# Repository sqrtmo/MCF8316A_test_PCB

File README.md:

# MCF8316A test board (KiCAD version)

This is meant to be an easy and cheaper way to test the MCF8316A chip. If you do not have access, 
or you don't want to buy the evaluation board from TI(see datasheet in doc subfolder), 
you can use this PCB in combiation [with my micropython driver made for raspberry pi pico](https://github.com/sqrtmo/MCF8316A_driver?tab=readme-ov-file) to setup and 
test the chip with your desired BLDC motor.

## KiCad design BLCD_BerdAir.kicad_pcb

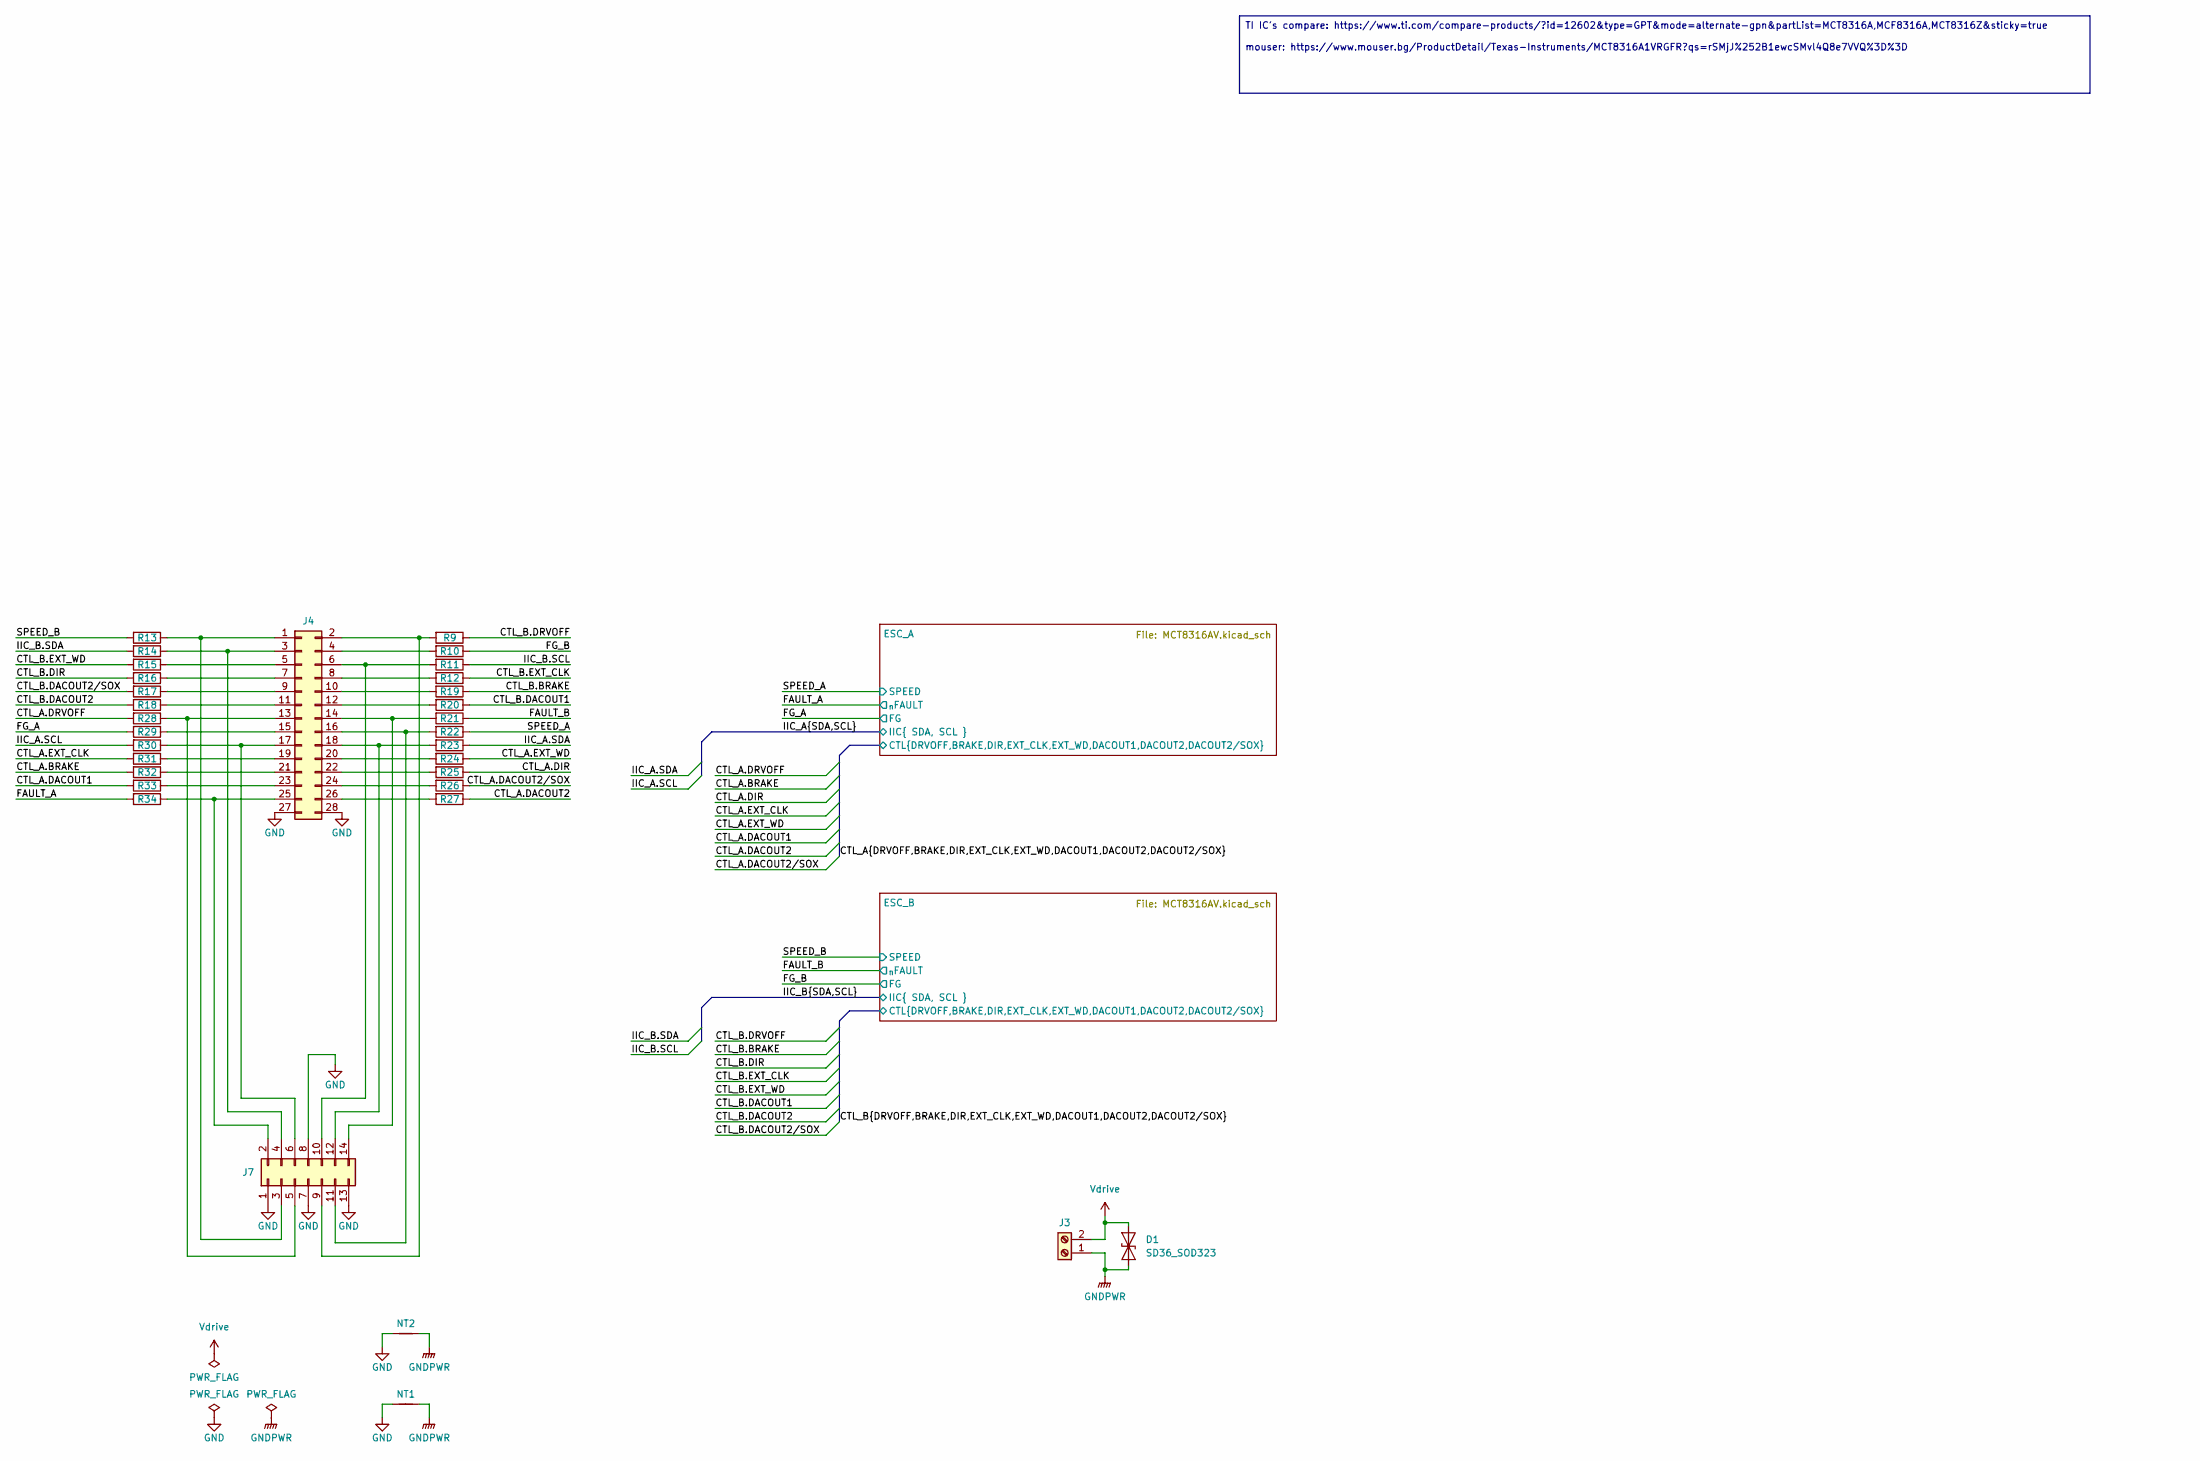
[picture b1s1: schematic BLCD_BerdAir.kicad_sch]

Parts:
D1: SD36_SOD323; D_SOD-323
J3: Screw_Terminal_01x03; TerminalBlock_Phoenix_MKDS-1,5-2-5.08_1x02_P5.08mm_Horizont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
J4: Conn_02x12_Odd_Even; PinHeader_2x14_P2.54mm_Vertical
J7: Conn_02x06_Top_Bottom; PinHeader_2x07_P2.54mm_Vertical
NT1, NT2: NetTie_2; NetTie-2_SMD_Pad0.5mm
R9, R10, R11, R12, R13, R14, R15, R16, R17, R18, R19, R20, R21, R22, R23, R24, R25, R26, R27, R28, R29, R30, R31, R32, R33, R34: 100R; R_0402_1005Metric

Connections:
/CTL_A.BRAKE: R32.2; also elsewhere on the board
/CTL_A.DACOUT1: R33.2; also elsewhere on the board
/CTL_A.DACOUT2: R27.1; also elsewhere on the board
/CTL_A.DACOUT2/SOX: R26.1; also elsewhere on the board
/CTL_A.DIR: R25.1; also elsewhere on the board
/CTL_A.DRVOFF: R28.2; also elsewhere on the board
/CTL_A.EXT_CLK: R31.2; also elsewhere on the board
/CTL_A.EXT_WD: R24.1; also elsewhere on the board
/CTL_B.BRAKE: R19.1; also elsewhere on the board
/CTL_B.DACOUT1: R20.1; also elsewhere on the board
/CTL_B.DACOUT2: R18.2; also elsewhere on the board
/CTL_B.DACOUT2/SOX: R17.2; also elsewhere on the board
/CTL_B.DIR: R16.2; also elsewhere on the board
/CTL_B.DRVOFF: R9.1; also elsewhere on the board
/CTL_B.EXT_CLK: R12.1; also elsewhere on the board
/CTL_B.EXT_WD: R15.2; also elsewhere on the board
/FAULT_A: R34.2; also elsewhere on the board
/FAULT_B: R21.1; also elsewhere on the board
/FG_A: R29.2; also elsewhere on the board
/FG_B: R10.1; also elsewhere on the board
/IIC_A.SCL: R30.2; also elsewhere on the board
/IIC_A.SDA: R23.1; also elsewhere on the board
/IIC_B.SCL: R11.1; also elsewhere on the board
/IIC_B.SDA: R14.2; also elsewhere on the board
/SPEED_A: R22.1; also elsewhere on the board
/SPEED_B: R13.2; also elsewhere on the board
GND: J4.27, J4.28, J7.1, J7.7, J7.8, J7.13, NT1.1, NT2.1; also elsewhere on the board
GNDPWR: D1.1 (A1), J3.1, NT1.2, NT2.2; also elsewhere on the board
unnamed: J4.1, J7.3, R13.1
unnamed: J4.2, J7.9, R9.2
unnamed: J4.3, J7.4, R14.1
unnamed: J4.4, R10.2
unnamed: J4.5, R15.1
unnamed: J4.6, J7.10, R11.2
unnamed: J4.7, R16.1
unnamed: J4.8, R12.2
unnamed: J4.9, R17.1
unnamed: J4.10, R19.2
unnamed: J4.11, R18.1
unnamed: J4.12, R20.2
unnamed: J4.13, J7.5, R28.1
unnamed: J4.14, J7.14, R21.2
unnamed: J4.15, R29.1
unnamed: J4.16, J7.11, R22.2
unnamed: J4.17, J7.6, R30.1
unnamed: J4.18, J7.12, R23.2
unnamed: J4.19, R31.1
unnamed: J4.20, R24.2
unnamed: J4.21, R32.1
unnamed: J4.22, R25.2
unnamed: J4.23, R33.1
unnamed: J4.24, R26.2
unnamed: J4.25, J7.2, R34.1
unnamed: J4.26, R27.2
Vdrive: D1.2 (A2), J3.2; also elsewhere on the board

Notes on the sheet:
TI IC's compare: https://www.ti.com/compare-products/?id=12602&type=GPT&mode=alternate-gpn&partList=MCT8316A,MCF8316A,MCT8316Z&sticky=true mouser: https://www.mouser.bg/ProductDetail/Texas-Instruments/MCT8316A1VRGFR?qs=rSMjJ%252B1ewcSMvl4Q8e7VVQ%3D%3D

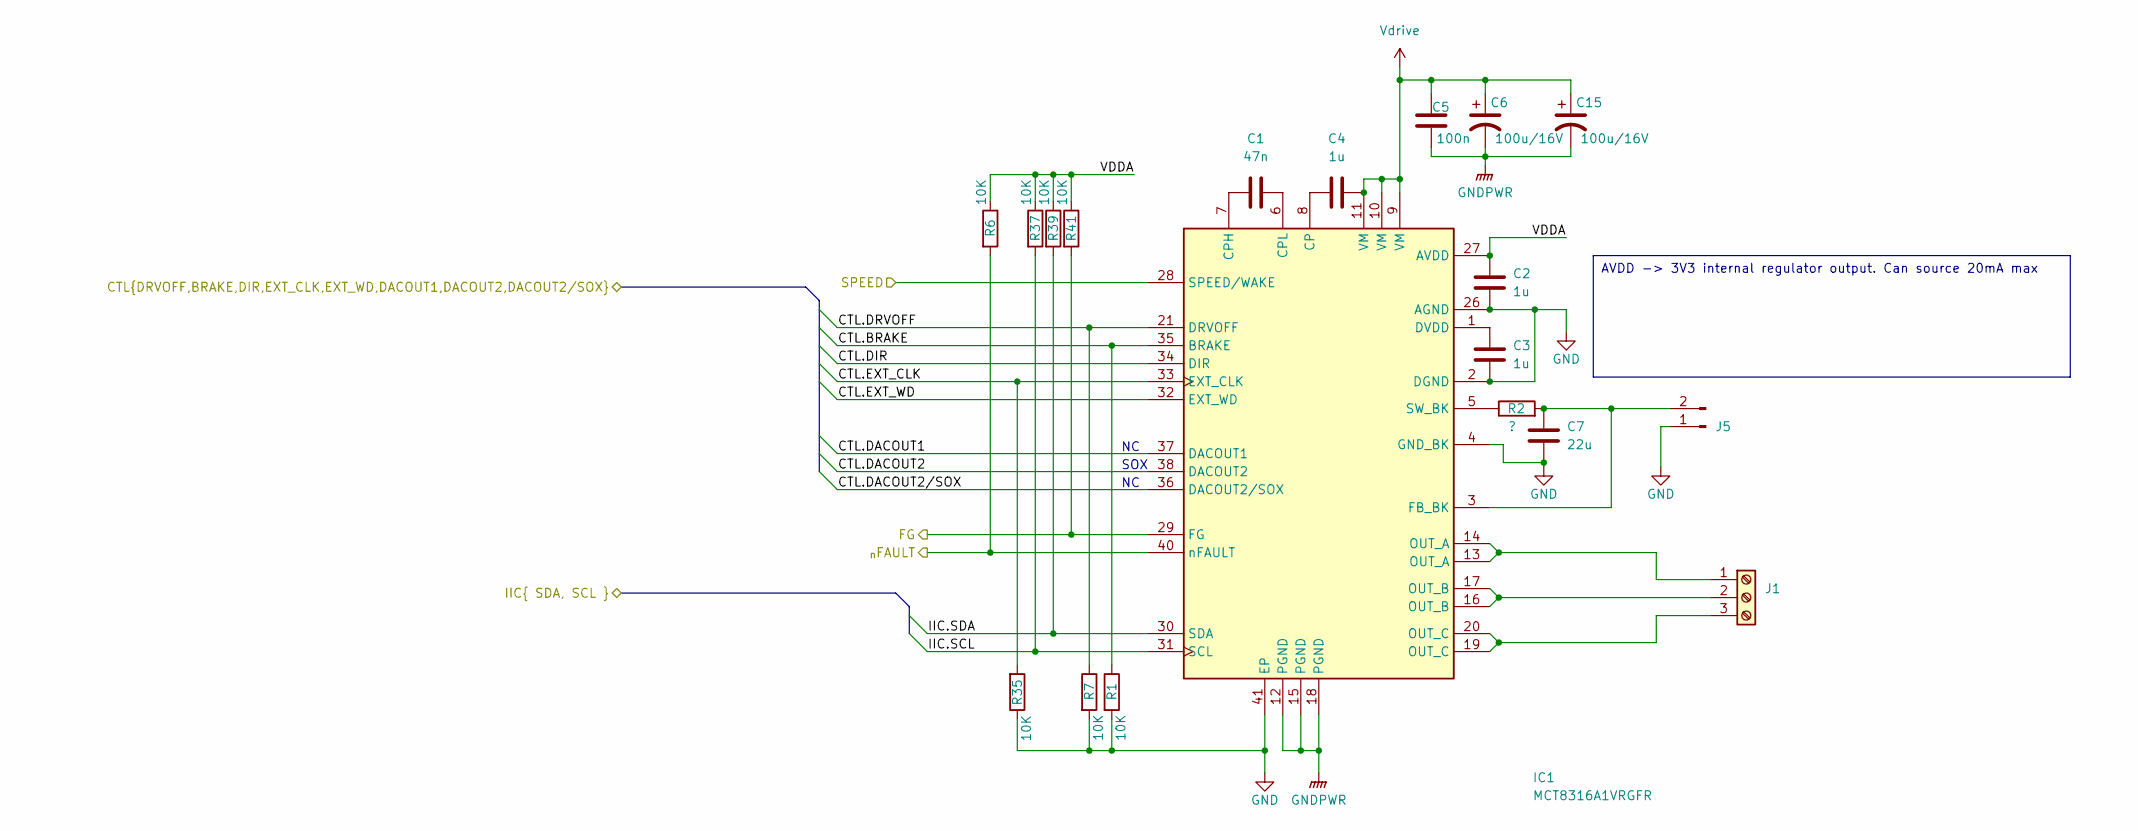
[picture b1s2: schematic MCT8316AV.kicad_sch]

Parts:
C1: 47n; C_0402_1005Metric
C2, C3, C4: 1u; C_0402_1005Metric
C5: 100n; C_0603_1608Metric
C6, C15: 100u/16V; CP_EIA-7132-28_AVX-C
C7: 22u; C_0603_1608Metric
IC1: MCT8316A1VRGFR; QFN50P500X700X100-41N-D; Manufacturer_Part_Number MCT8316A1VRGFR; Mouser Part Number 595-MCT8316A1VRGFR
J1: Screw_Terminal_01x03; TerminalBlock_Phoenix_MKDS-1,5-3-5.08_1x03_P5.08mm_Horizont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
J5: Conn_01x02_Pin; PinHeader_1x02_P1.27mm_Vertical
R1, R6, R7, R35, R37, R39, R41: 10K; R_0402_1005Metric
R2: ?; R_1210_3225Metric

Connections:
/CTL_A.BRAKE: IC1.35 (BRAKE), R1.1; also elsewhere on the board
/CTL_A.DACOUT1: IC1.37 (DACOUT1); also elsewhere on the board
/CTL_A.DACOUT2: IC1.38 (DACOUT2); also elsewhere on the board
/CTL_A.DACOUT2/SOX: IC1.36 (DACOUT2/SOX); also elsewhere on the board
/CTL_A.DIR: IC1.34 (DIR); also elsewhere on the board
/CTL_A.DRVOFF: IC1.21 (DRVOFF), R7.1; also elsewhere on the board
/CTL_A.EXT_CLK: IC1.33 (EXT_CLK), R35.2; also elsewhere on the board
/CTL_A.EXT_WD: IC1.32 (EXT_WD); also elsewhere on the board
/ESC_A/VDDA: C2.2, IC1.27 (AVDD), R6.1, R37.1, R39.1, R41.1
/FAULT_A: IC1.40 (nFAULT), R6.2; also elsewhere on the board
/FG_A: IC1.29 (FG), R41.2; also elsewhere on the board
/IIC_A.SCL: IC1.31 (SCL), R37.2; also elsewhere on the board
/IIC_A.SDA: IC1.30 (SDA), R39.2; also elsewhere on the board
/SPEED_A: IC1.28 (SPEED/WAKE); also elsewhere on the board
GND: C2.1, C3.1, C7.1, IC1.2 (DGND), IC1.4 (GND_BK), IC1.26 (AGND), IC1.41 (EP), J5.1, R1.2, R7.2, R35.1; also elsewhere on the board
GNDPWR: C5.1, C6.2, C15.2, IC1.12 (PGND), IC1.15 (PGND), IC1.18 (PGND); also elsewhere on the board
unnamed: C4.1, IC1.8 (CP)
unnamed: C1.1, IC1.7 (CPH)
unnamed: C1.2, IC1.6 (CPL)
unnamed: C3.2, IC1.1 (DVDD)
unnamed: C7.2, IC1.3 (FB_BK), J5.2, R2.2
unnamed: IC1.5 (SW_BK), R2.1
unnamed: IC1.13 (OUT_A), IC1.14 (OUT_A), J1.1
unnamed: IC1.16 (OUT_B), IC1.17 (OUT_B), J1.2
unnamed: IC1.19 (OUT_C), IC1.20 (OUT_C), J1.3
Vdrive: C4.2, C5.2, C6.1, C15.1, IC1.9 (VM), IC1.10 (VM), IC1.11 (VM); also elsewhere on the board

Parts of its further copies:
C8: 47n; C_0402_1005Metric
C9, C12, C13: 1u; C_0402_1005Metric
C10: 100n; C_0603_1608Metric
C11, C16: 100u/16V; CP_EIA-7132-28_AVX-C
C14: 22u; C_0603_1608Metric
IC2: MCT8316A1VRGFR; QFN50P500X700X100-41N-D; Manufacturer_Part_Number MCT8316A1VRGFR; Mouser Part Number 595-MCT8316A1VRGFR
J2: Screw_Terminal_01x03; TerminalBlock_Phoenix_MKDS-1,5-3-5.08_1x03_P5.08mm_Horizont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
J6: Conn_01x02_Pin; PinHeader_1x02_P1.27mm_Vertical
R3, R4, R5, R36, R38, R40, R42: 10K; R_0402_1005Metric
R8: ?; R_1210_3225Metric

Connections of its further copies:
/CTL_B.BRAKE: IC2.35 (BRAKE), R5.1; also elsewhere on the board
/CTL_B.DACOUT1: IC2.37 (DACOUT1); also elsewhere on the board
/CTL_B.DACOUT2: IC2.38 (DACOUT2); also elsewhere on the board
/CTL_B.DACOUT2/SOX: IC2.36 (DACOUT2/SOX); also elsewhere on the board
/CTL_B.DIR: IC2.34 (DIR); also elsewhere on the board
/CTL_B.DRVOFF: IC2.21 (DRVOFF), R4.1; also elsewhere on the board
/CTL_B.EXT_CLK: IC2.33 (EXT_CLK), R36.2; also elsewhere on the board
/CTL_B.EXT_WD: IC2.32 (EXT_WD); also elsewhere on the board
/ESC_B/VDDA: C12.2, IC2.27 (AVDD), R3.1, R38.1, R40.1, R42.1
/FAULT_B: IC2.40 (nFAULT), R3.2; also elsewhere on the board
/FG_B: IC2.29 (FG), R42.2; also elsewhere on the board
/IIC_B.SCL: IC2.31 (SCL), R38.2; also elsewhere on the board
/IIC_B.SDA: IC2.30 (SDA), R40.2; also elsewhere on the board
/SPEED_B: IC2.28 (SPEED/WAKE); also elsewhere on the board
GND: C12.1, C13.1, C14.1, IC2.2 (DGND), IC2.4 (GND_BK), IC2.26 (AGND), IC2.41 (EP), J6.1, R4.2, R5.2, R36.1; also elsewhere on the board
GNDPWR: C10.1, C11.2, C16.2, IC2.12 (PGND), IC2.15 (PGND), IC2.18 (PGND); also elsewhere on the board
unnamed: C9.1, IC2.8 (CP)
unnamed: C8.1, IC2.7 (CPH)
unnamed: C8.2, IC2.6 (CPL)
unnamed: C13.2, IC2.1 (DVDD)
unnamed: C14.2, IC2.3 (FB_BK), J6.2, R8.2
unnamed: IC2.5 (SW_BK), R8.1
unnamed: IC2.13 (OUT_A), IC2.14 (OUT_A), J2.1
unnamed: IC2.16 (OUT_B), IC2.17 (OUT_B), J2.2
unnamed: IC2.19 (OUT_C), IC2.20 (OUT_C), J2.3
Vdrive: C9.2, C10.2, C11.1, C16.1, IC2.9 (VM), IC2.10 (VM), IC2.11 (VM); also elsewhere on the board

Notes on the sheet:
AVDD -> 3V3 internal regulator output. Can source 20mA max
SOX

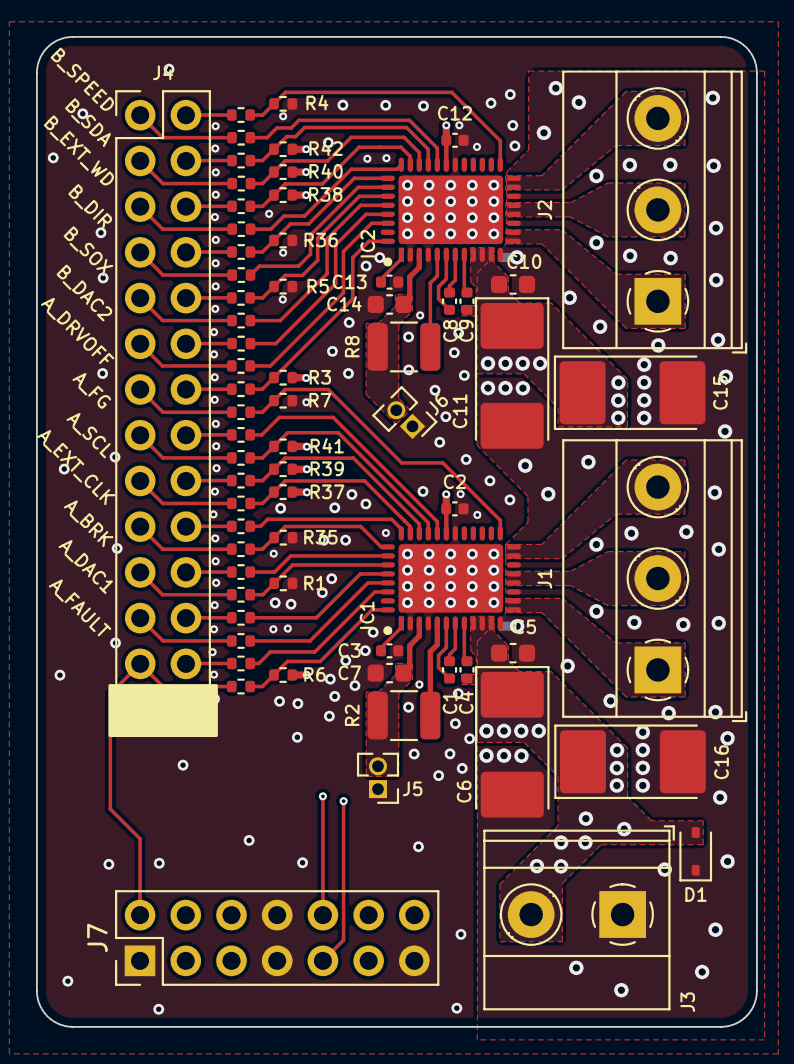
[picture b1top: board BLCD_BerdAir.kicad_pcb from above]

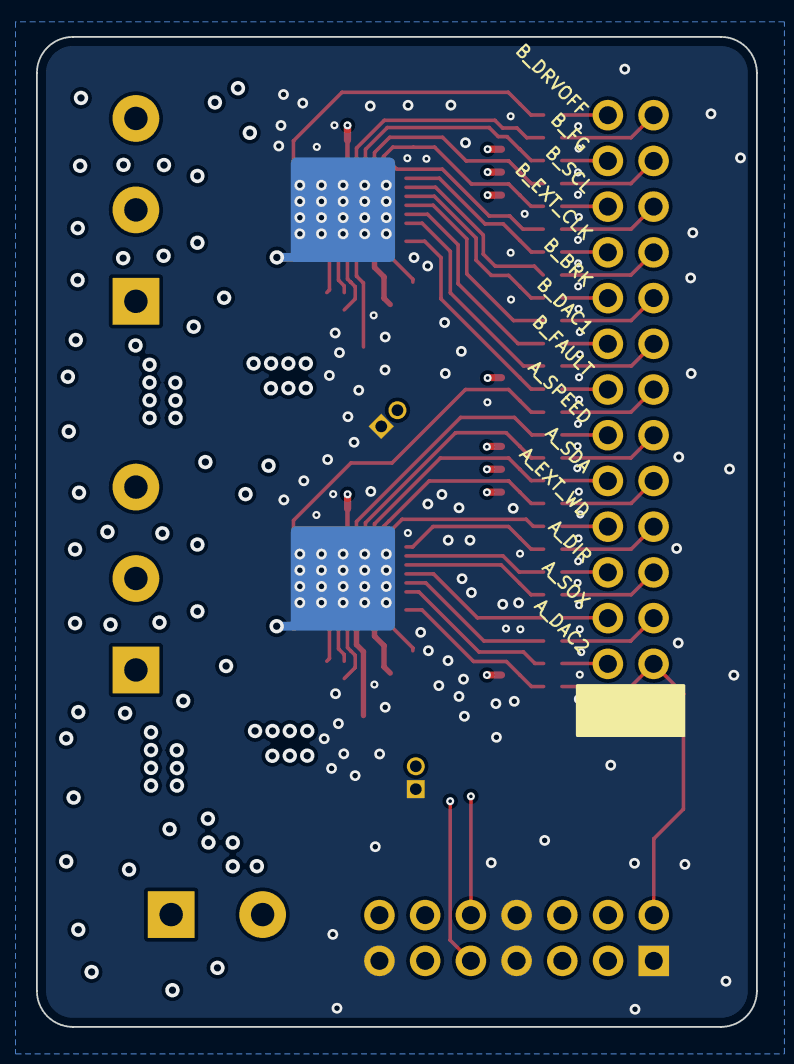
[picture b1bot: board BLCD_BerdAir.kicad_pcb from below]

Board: 4 copper layers, 40.0 x 55.0 mm, 70 parts (2 on the bottom side), 75 nets.

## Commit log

2024-01-17 init
2024-05-25 tested
2024-05-25 link
